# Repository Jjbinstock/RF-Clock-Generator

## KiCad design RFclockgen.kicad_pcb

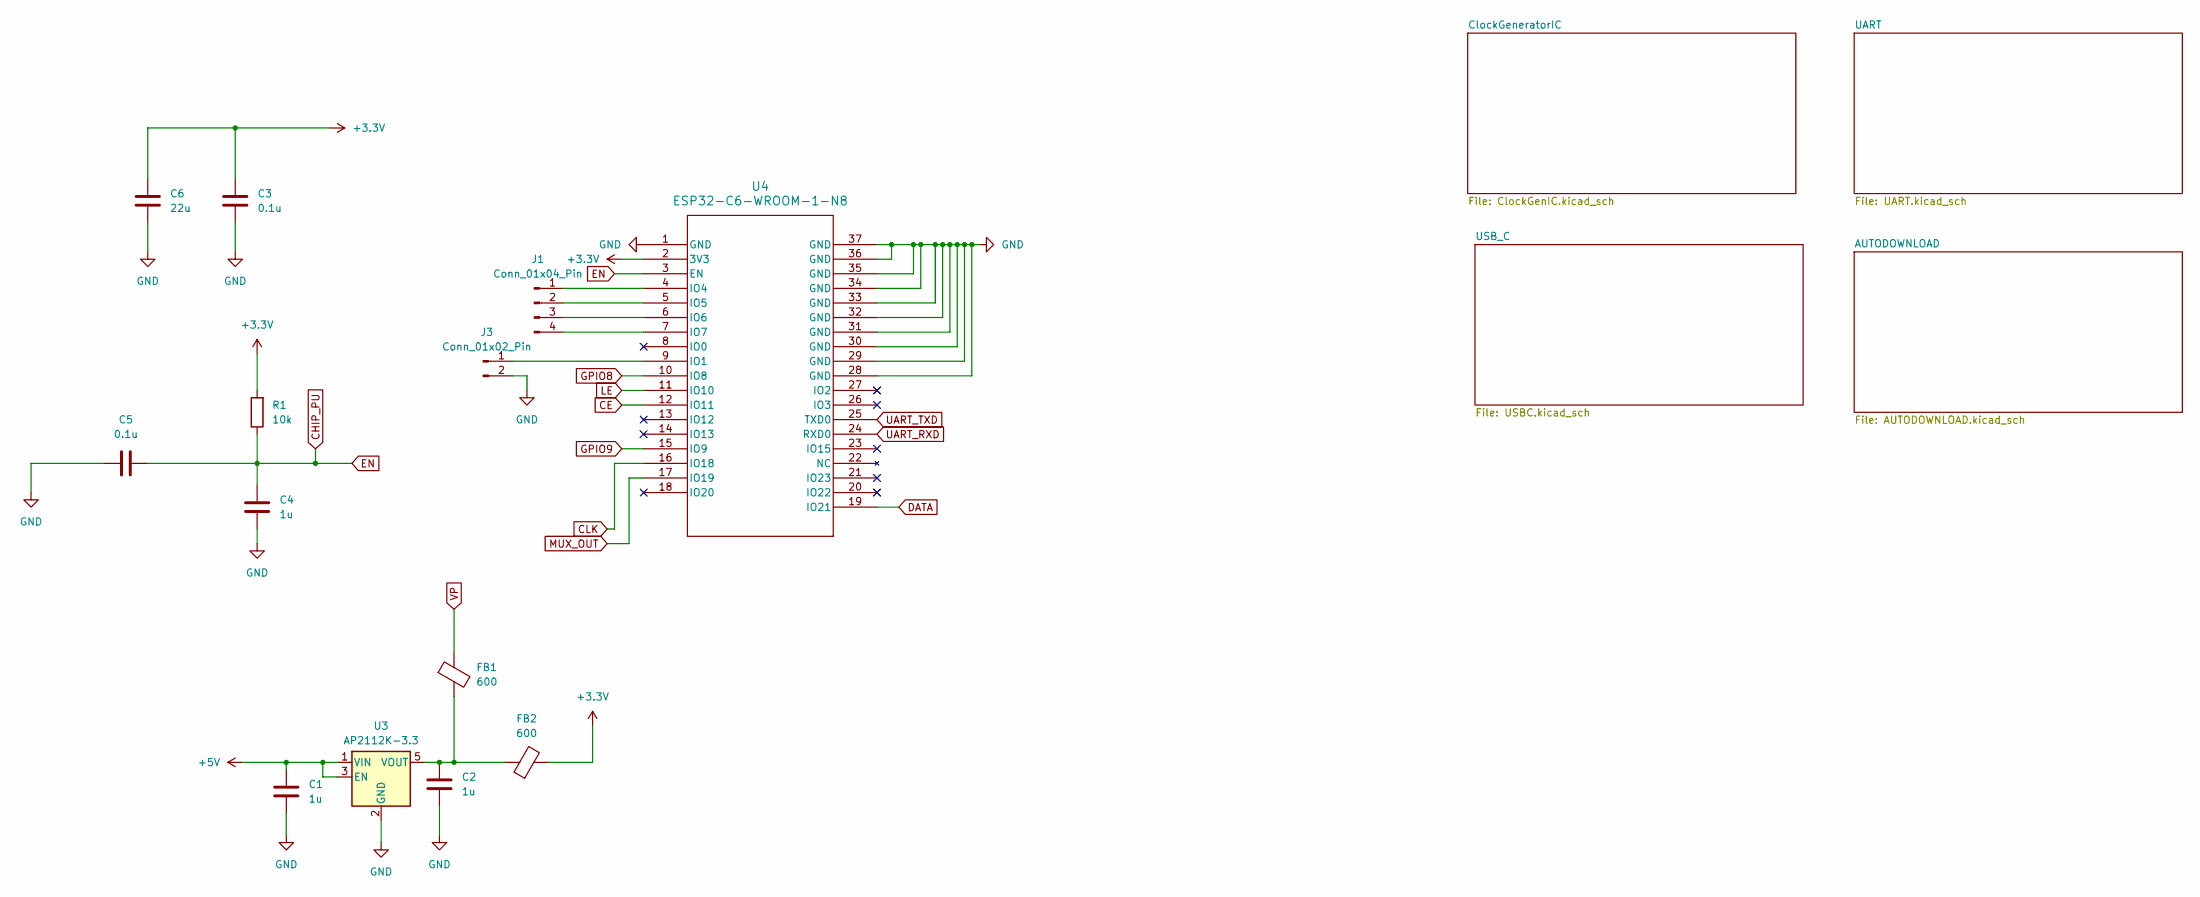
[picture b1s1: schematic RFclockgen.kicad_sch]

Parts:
C1, C2, C4: 1u; C_0805_2012Metric_Pad1.18x1.45mm_HandSolder
C3, C5: 0.1u; C_0805_2012Metric_Pad1.18x1.45mm_HandSolder
C6: 22u; C_0805_2012Metric_Pad1.18x1.45mm_HandSolder
FB1, FB2: 600; L_1206_3216Metric_Pad1.22x1.90mm_HandSolder
J1: Conn_01x04_Pin; PinHeader_1x04_P1.00mm_Vertical
J3: Conn_01x02_Pin; PinHeader_1x02_P1.00mm_Vertical
R1: 10k; R_1206_3216Metric_Pad1.30x1.75mm_HandSolder
U3: AP2112K-3.3; SOT-23-5
U4: ESP32-C6-WROOM-1-N8; MOD28_ESP32-C6-WROOM-1_EXP

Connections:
+3.3V: C3.1, C6.1, FB2.2, R1.2, U4.2 (3V3); also elsewhere on the board
+5V: C1.1, U3.1 (VIN), U3.3 (EN); also elsewhere on the board
CE: U4.12 (IO11); also elsewhere on the board
CHIP_PU: C4.1, C5.2, R1.1, U4.3 (EN); also elsewhere on the board
CLK: U4.16 (IO18); also elsewhere on the board
DATA: U4.19 (IO21); also elsewhere on the board
GND: C1.2, C2.2, C3.2, C4.2, C5.1, C6.2, J3.2, U3.2 (GND), U4.1 (GND), U4.28 (GND), U4.29 (GND), U4.30 (GND), U4.31 (GND), U4.32 (GND), U4.33 (GND), U4.34 (GND), U4.35 (GND), U4.36 (GND), U4.37 (GND); also elsewhere on the board
GPIO8: U4.10 (IO8); also elsewhere on the board
GPIO9: U4.15 (IO9); also elsewhere on the board
LE: U4.11 (IO10); also elsewhere on the board
MUX_OUT: U4.17 (IO19); also elsewhere on the board
unnamed: J1.1, U4.4 (IO4)
unnamed: J1.2, U4.5 (IO5)
unnamed: J1.3, U4.6 (IO6)
unnamed: J1.4, U4.7 (IO7)
unnamed: J3.1, U4.9 (IO1)
unnamed: C2.1, FB1.2, FB2.1, U3.5 (VOUT)
UART_RXD: U4.24 (RXD0); also elsewhere on the board
UART_TXD: U4.25 (TXD0); also elsewhere on the board
VP: FB1.1; also elsewhere on the board

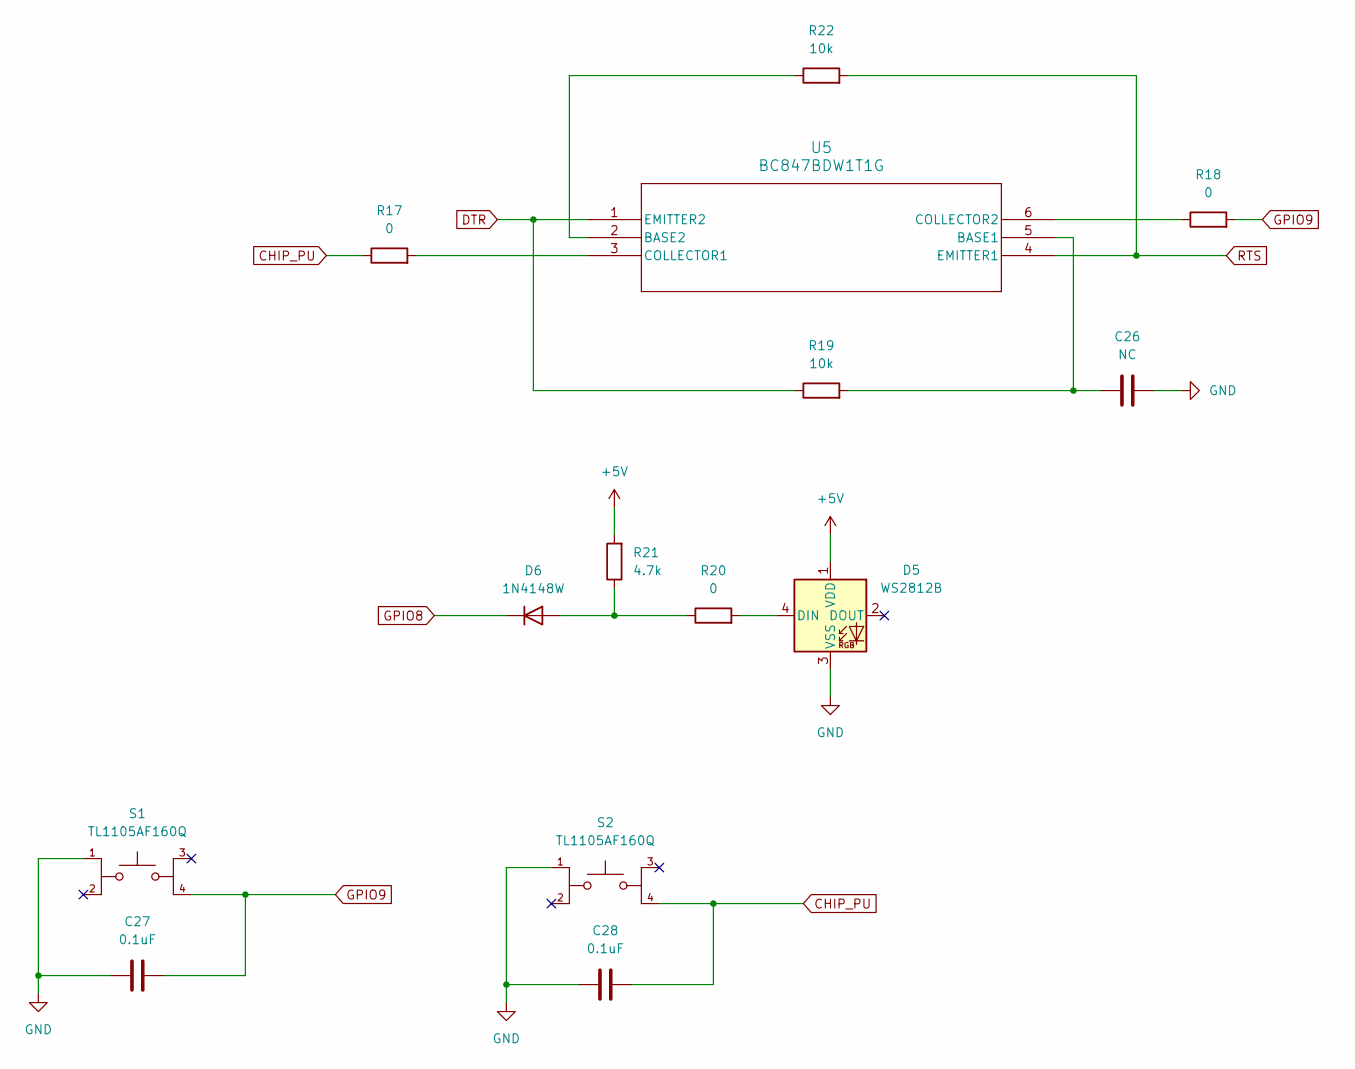
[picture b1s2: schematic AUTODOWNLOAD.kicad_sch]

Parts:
C26: NC; C_0805_2012Metric_Pad1.18x1.45mm_HandSolder
C27, C28: 0.1uF; C_0805_2012Metric_Pad1.18x1.45mm_HandSolder
D5: WS2812B; LED_WS2812B_PLCC4_5.0x5.0mm_P3.2mm
D6: 1N4148W; D_SOD-123
R17, R18, R20: 0; R_1206_3216Metric_Pad1.30x1.75mm_HandSolder
R19, R22: 10k; R_1206_3216Metric_Pad1.30x1.75mm_HandSolder
R21: 4.7k; R_1206_3216Metric_Pad1.30x1.75mm_HandSolder
S1, S2: TL1105AF160Q; SW_TL1105AF160Q; PARTREV A
U5: BC847BDW1T1G; SOT-363-6_2P2X1P35_ONS

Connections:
+5V: D5.1 (VDD), R21.2; also elsewhere on the board
CHIP_PU: C28.2, R17.1, S2.4; also elsewhere on the board
DTR: R19.1, U5.1 (EMITTER2); also elsewhere on the board
GND: C26.2, C27.1, C28.1, D5.3 (VSS), S1.1, S2.1; also elsewhere on the board
GPIO8: D6.1 (K); also elsewhere on the board
GPIO9: C27.2, R18.2, S1.4; also elsewhere on the board
unnamed: D5.4 (DIN), R20.2
unnamed: D6.2 (A), R20.1, R21.1
unnamed: C26.1, R19.2, U5.5 (BASE1)
unnamed: R22.1, U5.2 (BASE2)
unnamed: R17.2, U5.3 (COLLECTOR1)
unnamed: R18.1, U5.6 (COLLECTOR2)
RTS: R22.2, U5.4 (EMITTER1); also elsewhere on the board

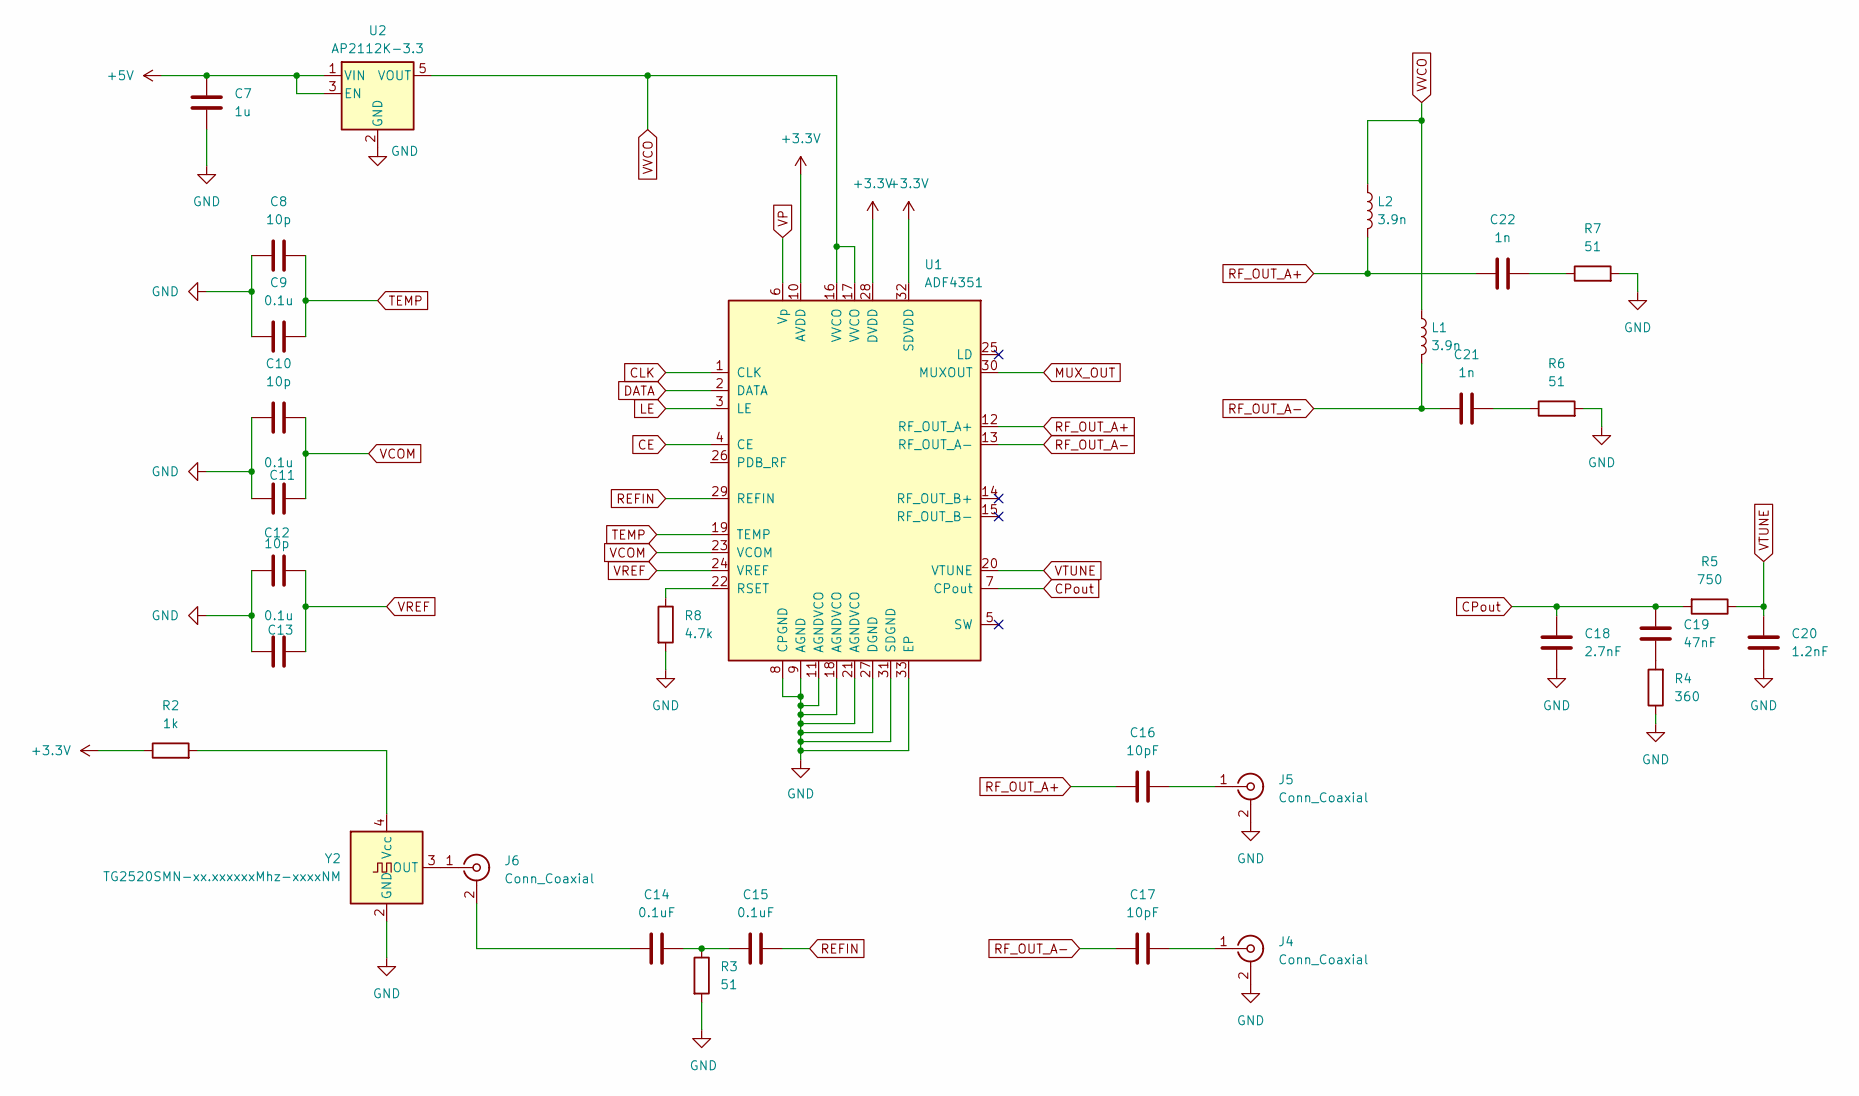
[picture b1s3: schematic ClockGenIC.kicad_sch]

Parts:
C7: 1u; C_0805_2012Metric_Pad1.18x1.45mm_HandSolder
C8, C10, C12: 10p; C_0805_2012Metric_Pad1.18x1.45mm_HandSolder
C9, C11, C13: 0.1u; C_0805_2012Metric_Pad1.18x1.45mm_HandSolder
C14, C15: 0.1uF; C_0805_2012Metric_Pad1.18x1.45mm_HandSolder
C16, C17: 10pF; C_0805_2012Metric_Pad1.18x1.45mm_HandSolder
C18: 2.7nF; C_0805_2012Metric_Pad1.18x1.45mm_HandSolder
C19: 47nF; C_0805_2012Metric_Pad1.18x1.45mm_HandSolder
C20: 1.2nF; C_0805_2012Metric_Pad1.18x1.45mm_HandSolder
C21, C22: 1n; C_0805_2012Metric_Pad1.18x1.45mm_HandSolder
J4, J5, J6: Conn_Coaxial; SMA_Samtec_SMA-J-P-H-ST-EM1_EdgeMount
L1, L2: 3.9n; L_1206_3216Metric_Pad1.22x1.90mm_HandSolder
R2: 1k; R_1206_3216Metric_Pad1.30x1.75mm_HandSolder
R3, R6, R7: 51; R_1206_3216Metric_Pad1.30x1.75mm_HandSolder
R4: 360; R_1206_3216Metric_Pad1.30x1.75mm_HandSolder
R5: 750; R_1206_3216Metric_Pad1.30x1.75mm_HandSolder
R8: 4.7k; R_1206_3216Metric_Pad1.30x1.75mm_HandSolder
U1: ADF4351; LFCSP-32-1EP_5x5mm_P0.5mm_EP3.25x3.25mm
U2: AP2112K-3.3; SOT-23-5
Y2: TG2520SMN-xx.xxxxxxMhz-xxxxNM; Oscillator_SMD_SeikoEpson_TG2520SMN-xxx-xxxxxx-4Pin_2.5x2.0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

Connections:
+3.3V: R2.1, U1.10 (AVDD), U1.28 (DVDD), U1.32 (SDVDD); also elsewhere on the board
+5V: C7.1, U2.1 (VIN), U2.3 (EN); also elsewhere on the board
CE: U1.4 (CE); also elsewhere on the board
CLK: U1.1 (CLK); also elsewhere on the board
CPout: C18.1, C19.1, R5.2, U1.7 (CPout)
DATA: U1.2 (DATA); also elsewhere on the board
GND: C7.2, C8.1, C9.1, C10.1, C11.1, C12.1, C13.1, C18.2, C20.2, J4.2 (Ext), J5.2 (Ext), R3.2, R4.1, R6.2, R7.2, R8.2, U1.8 (CPGND), U1.9 (AGND), U1.11 (AGNDVCO), U1.18 (AGNDVCO), U1.21 (AGNDVCO), U1.27 (DGND), U1.31 (SDGND), U1.33 (EP), U2.2 (GND), Y2.2 (GND); also elsewhere on the board
LE: U1.3 (LE); also elsewhere on the board
MUX_OUT: U1.30 (MUXOUT); also elsewhere on the board
unnamed: C14.1, C15.2, R3.1
unnamed: C19.2, R4.2
unnamed: C21.1, R6.1
unnamed: C22.1, R7.1
unnamed: C17.1, J4.1 (In)
unnamed: C16.1, J5.1 (In)
unnamed: C14.2, J6.2 (Ext)
unnamed: J6.1 (In), Y2.3 (OUT)
unnamed: R8.1, U1.22 (RSET)
unnamed: R2.2, Y2.4 (Vcc)
REFIN: C15.1, U1.29 (REFIN)
RF_OUT_A+: C16.2, C22.2, L2.2, U1.12 (RF_OUT_A+)
RF_OUT_A-: C17.2, C21.2, L1.2, U1.13 (RF_OUT_A-)
TEMP: C8.2, C9.2, U1.19 (TEMP)
VCOM: C10.2, C11.2, U1.23 (VCOM)
VP: U1.6 (Vp); also elsewhere on the board
VREF: C12.2, C13.2, U1.24 (VREF)
VTUNE: C20.1, R5.1, U1.20 (VTUNE)
VVCO: L1.1, L2.1, U1.16 (VVCO), U1.17 (VVCO), U2.5 (VOUT)

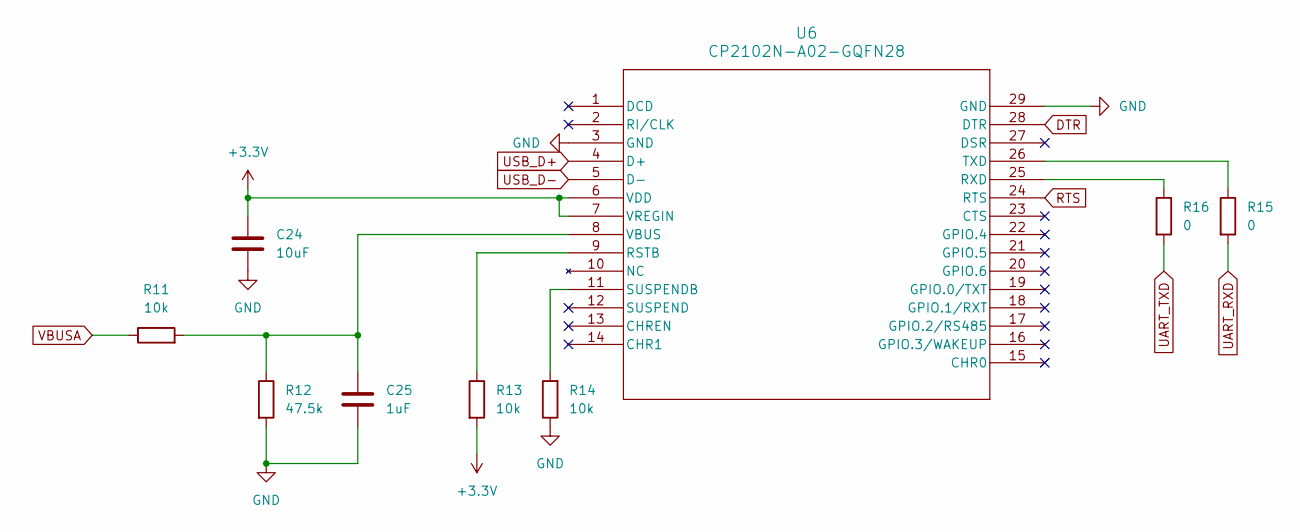
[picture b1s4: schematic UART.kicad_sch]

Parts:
C24: 10uF; C_0805_2012Metric_Pad1.18x1.45mm_HandSolder
C25: 1uF; C_0805_2012Metric_Pad1.18x1.45mm_HandSolder
R11, R13, R14: 10k; R_1206_3216Metric_Pad1.30x1.75mm_HandSolder
R12: 47.5k; R_1206_3216Metric_Pad1.30x1.75mm_HandSolder
R15, R16: 0; R_1206_3216Metric_Pad1.30x1.75mm_HandSolder
U6: CP2102N-A02-GQFN28; QFN28_5X5

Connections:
+3.3V: C24.2, R13.2, U6.6 (VDD), U6.7 (VREGIN); also elsewhere on the board
DTR: U6.28 (DTR); also elsewhere on the board
GND: C24.1, C25.2, R12.2, R14.1, U6.3 (GND), U6.29 (GND); also elsewhere on the board
unnamed: R13.1, U6.9 (RSTB)
unnamed: R16.1, U6.25 (RXD)
unnamed: R14.2, U6.11 (SUSPENDB)
unnamed: R15.1, U6.26 (TXD)
unnamed: C25.1, R11.2, R12.1, U6.8 (VBUS)
RTS: U6.24 (RTS); also elsewhere on the board
UART_RXD: R15.2; also elsewhere on the board
UART_TXD: R16.2; also elsewhere on the board
USB_D+: U6.4 (D+); also elsewhere on the board
USB_D-: U6.5 (D-); also elsewhere on the board
VBUSA: R11.1; also elsewhere on the board

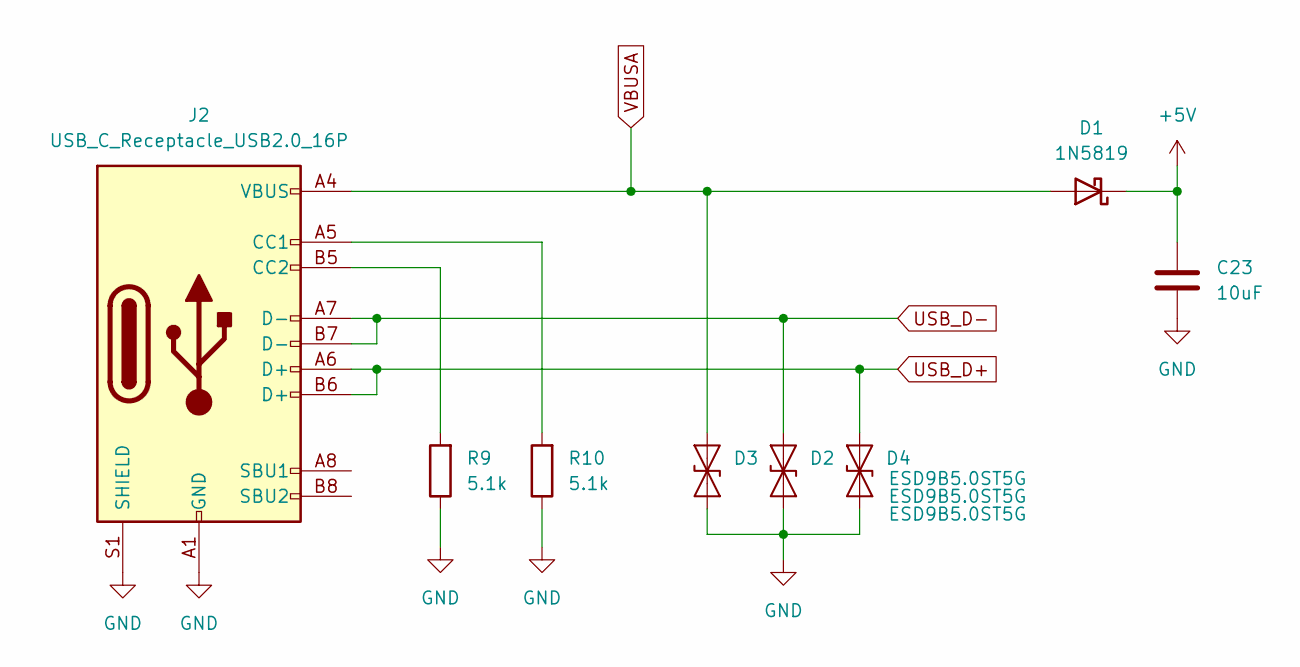
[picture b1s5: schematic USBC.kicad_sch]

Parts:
C23: 10uF; C_0805_2012Metric_Pad1.18x1.45mm_HandSolder
D1: 1N5819; D_DO-41_SOD81_P10.16mm_Horizontal
D2, D3, D4: ESD9B5.0ST5G; D_SOD-923
J2: USB_C_Receptacle_USB2.0_16P
R9, R10: 5.1k; R_1206_3216Metric_Pad1.30x1.75mm_HandSolder

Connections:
+5V: C23.1, D1.1 (K); also elsewhere on the board
GND: C23.2, D2.1 (A1), D3.1 (A1), D4.1 (A1), J2.A1 (GND), J2.A12 (GND), J2.B1 (GND), J2.B12 (GND), J2.S1 (SHIELD), R9.1, R10.1; also elsewhere on the board
unnamed: J2.A5 (CC1), R10.2
unnamed: J2.B5 (CC2), R9.2
USB_D+: D4.2 (A2), J2.A6 (D+), J2.B6 (D+); also elsewhere on the board
USB_D-: D2.2 (A2), J2.A7 (D-), J2.B7 (D-); also elsewhere on the board
VBUSA: D1.2 (A), D3.2 (A2), J2.A4 (VBUS), J2.A9 (VBUS), J2.B4 (VBUS), J2.B9 (VBUS); also elsewhere on the board

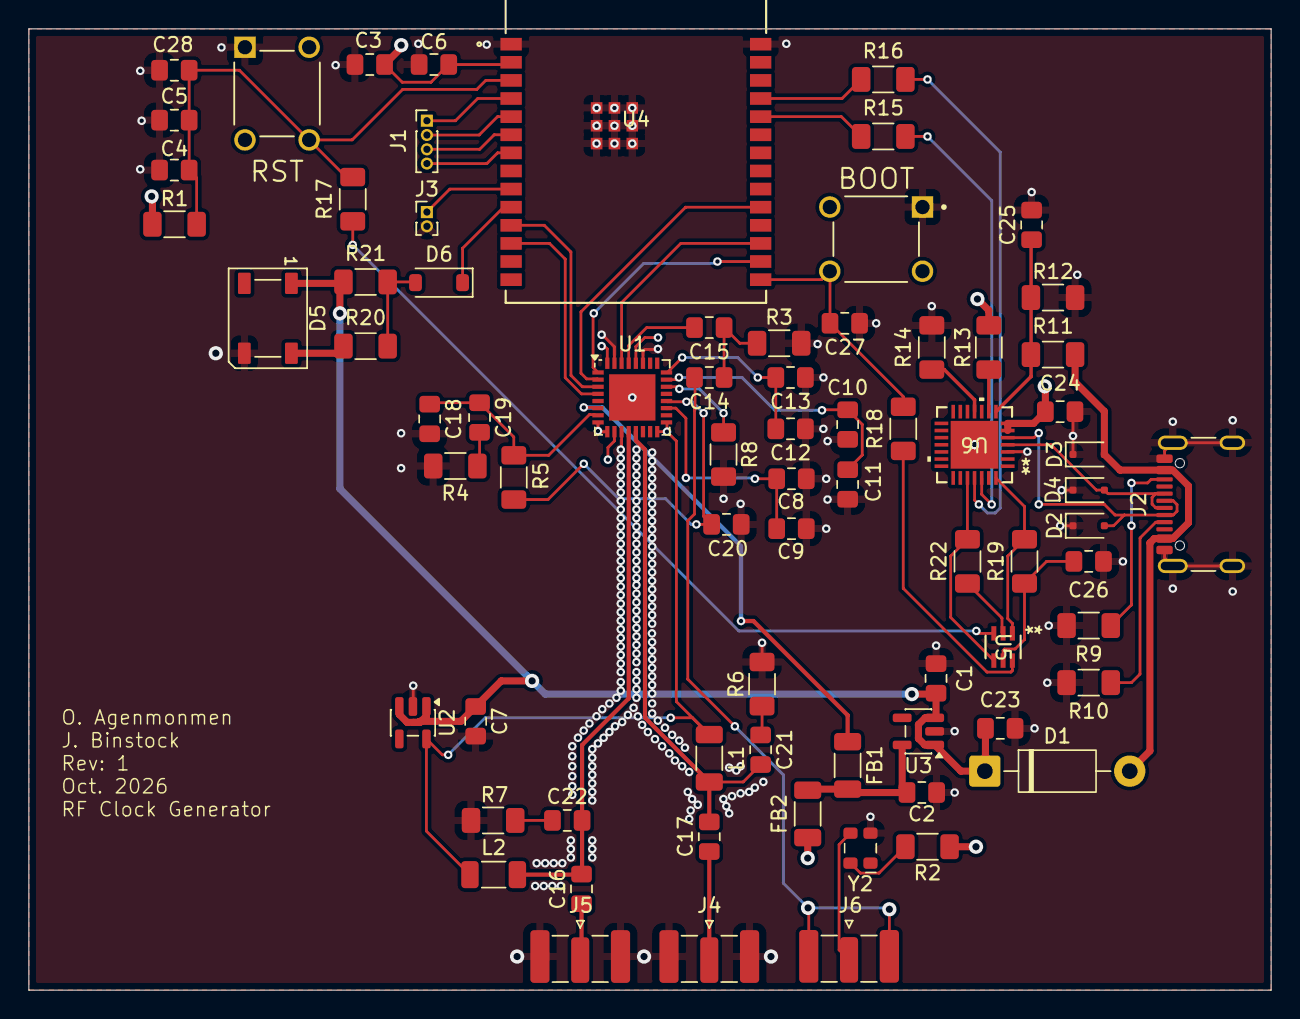
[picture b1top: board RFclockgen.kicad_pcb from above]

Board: 4 copper layers, 87.1 x 67.4 mm, 75 parts (0 on the bottom side), 57 nets.

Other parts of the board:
BOOT: TL1105AF160Q; SW_TL1105AF160Q
RST: TL1105AF160Q; SW_TL1105AF160Q

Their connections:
CHIP_PU: RST.4; also elsewhere on the board
GND: BOOT.1, RST.1; also elsewhere on the board
GPIO9: BOOT.4; also elsewhere on the board
